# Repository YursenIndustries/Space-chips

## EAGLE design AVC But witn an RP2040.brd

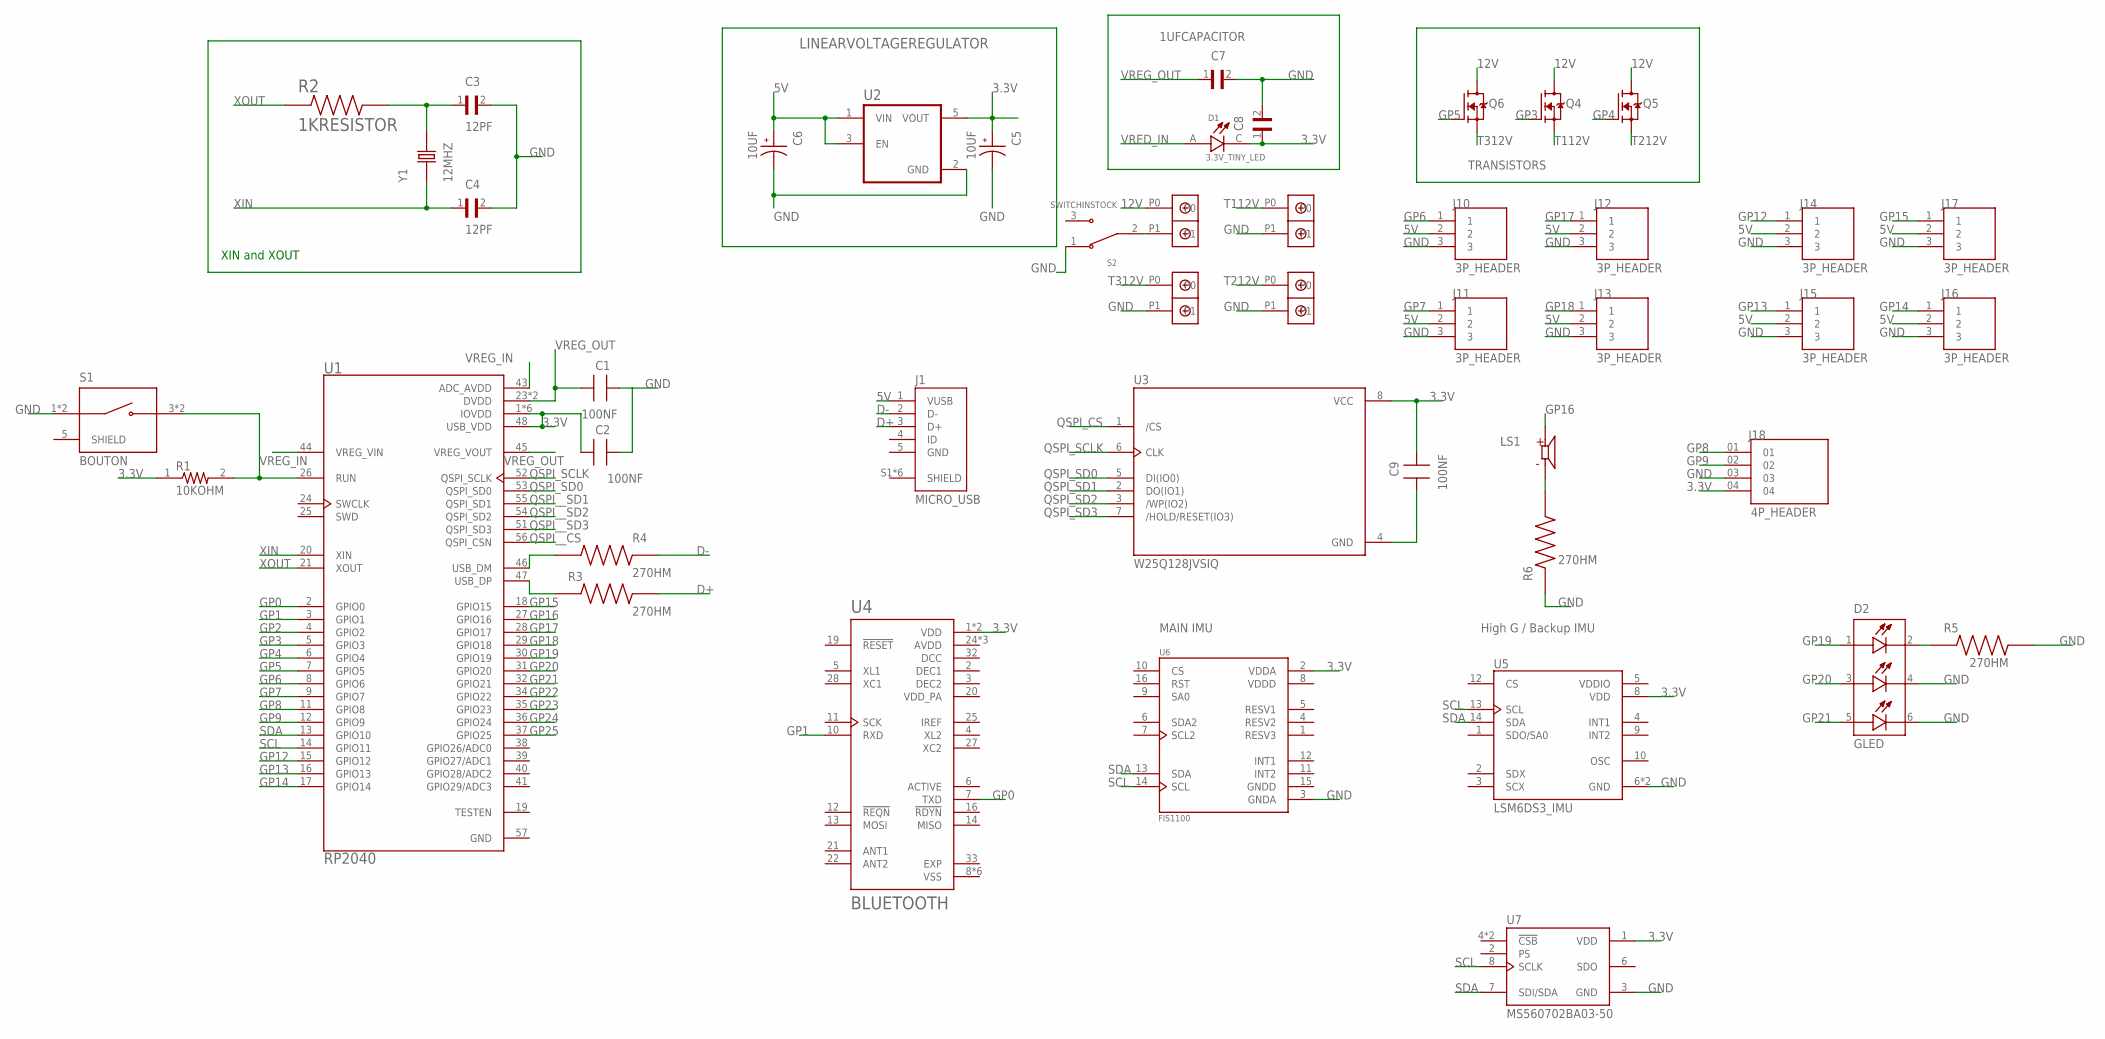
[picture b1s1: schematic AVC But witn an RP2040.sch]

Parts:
C1, C2, C9: 100NF; WCAP-CSST_885382207007
C3, C4: 12PF; CAPC1005X55N
C5, C6: 10UF; CAP_EEEFN1J100P
C7, C8: 1UFCAPACITOR
D1: 3.3V_TINY_LED; LED_IN-S124ARUW
D2: GLED
J1: MICRO_USB; FCI_10118193-0001LF
J10, J11, J12, J13, J14, J15, J16, J17: 3P_HEADER
J18: 4P_HEADER
LS1: 1.5V_BUZZER; SPKR_PKLCS1212E4001-R1
Q4, Q5, Q6: MOSFET20V; SOT95P240X111-3N
R1: 10KOHM; RESC1608X50N
R2: 1KRESISTOR
R3, R4, R5, R6: 270HM; RES_ERJU03F27R0V
S1: BOUTON; SW_1-1437565-9
S2: SWITCHINSTOCK; SW_EG1215AA
T_BATT: BLACK; BLACK`
T_PY1, T_PY2, T_PY3: BLACK; BLACK`
U1: RP2040; QFN40P700X700X90-57N
U2: LINEARVOLTAGEREGULATOR; SOT95P285X140-5N
U3: W25Q128JVSIQ; SOIC127P790X216-8N
U4: BLUETOOTH; QFN50P500X500X90-33N
U5: LSM6DS3_IMU; PQFN50P300X250X86-14N
U6: FIS1100; LGA16R50P4X4_330X330X100
U7: MS560702BA03-50; SON125P300X500X100-8N
Y1: 12MHZ; XTAL_ECS-120-S-5PX-TR

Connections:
3.3V: C2.1, C5.1, C8.1, C9.2, D1.C, J18.04, R1.1, U1.1 (IOVDD), U1.10 (IOVDD), U1.22 (IOVDD), U1.33 (IOVDD), U1.42 (IOVDD), U1.48 (USB_VDD), U1.49 (IOVDD), U2.5 (VOUT), U3.8 (VCC), U4.1 (VDD), U4.9 (VDD), U5.8 (VDD), U6.2 (VDDA), U7.1 (VDD)
5V: C6.1, J1.1 (VUSB), J10.2, J11.2, J12.2, J13.2, J14.2, J15.2, J16.2, J17.2, U2.1 (VIN), U2.3 (EN)
12V: Q4.3 (D), Q5.3 (D), Q6.3 (D), T_BATT.P0
AVDD: U4.24 (AVDD), U4.26 (AVDD), U4.29 (AVDD)
D+: J1.3 (D+), R3.2
D-: J1.2 (D-), R4.2
DCC: U4.32 (DCC)
DEC1: U4.2 (DEC1)
DEC2: U4.3 (DEC2)
EXP: U4.33 (EXP)
GND: C1.2, C2.2, C3.2, C4.2, C5.2, C6.2, C7.2, C8.2, D2.4 (GREEN_CATHODE), D2.6 (BLUE_CATHODE), J10.3, J11.3, J12.3, J13.3, J14.3, J15.3, J16.3, J17.3, J18.03, R5.2, R6.1, S1.1 (COM), S1.2 (COM), S2.1, T_PY1.P1, T_PY2.P1, T_PY3.P1, U1.57 (GND), U2.2 (GND), U5.6 (GND), U5.7 (GND), U6.3 (GNDA), U7.3 (GND)
GNDD: U6.15 (GNDD)
GP0: U1.2 (GPIO0), U4.7 (TXD)
GP1: U1.3 (GPIO1), U4.10 (RXD)
GP2: U1.4 (GPIO2)
GP3: Q4.1 (G), U1.5 (GPIO3)
GP4: Q5.1 (G), U1.6 (GPIO4)
GP5: Q6.1 (G), U1.7 (GPIO5)
GP6: J10.1, U1.8 (GPIO6)
GP7: J11.1, U1.9 (GPIO7)
GP8: J18.01, U1.11 (GPIO8)
GP9: J18.02, U1.12 (GPIO9)
GP12: J14.1, U1.15 (GPIO12)
GP13: J15.1, U1.16 (GPIO13)
GP14: J16.1, U1.17 (GPIO14)
GP15: J17.1, U1.18 (GPIO15)
GP16: LS1.P, U1.27 (GPIO16)
GP17: J12.1, U1.28 (GPIO17)
GP18: J13.1, U1.29 (GPIO18)
GP19: D2.1 (RED_ANODE), U1.30 (GPIO19)
GP20: D2.3 (GREEN_ANODE), U1.31 (GPIO20)
GP21: D2.5 (BLUE_ANODE), U1.32 (GPIO21)
GP22: U1.34 (GPIO22)
GP23: U1.35 (GPIO23)
GP24: U1.36 (GPIO24)
GP25: U1.37 (GPIO25)
unnamed: R1.2, S1.3 (NO), S1.4 (NO), U1.26 (RUN)
unnamed: C3.1, R2.2, Y1.2
unnamed: R3.1, U1.47 (USB_DP)
unnamed: C9.1, U3.4 (GND)
unnamed: R4.1, U1.46 (USB_DM)
unnamed: D2.2 (RED_CATHODE), R5.1
unnamed: LS1.N, R6.2
unnamed: S2.2, T_BATT.P1
QSPI_CS: U3.1 (/CS)
QSPI_SCLK: U1.52 (QSPI_SCLK), U3.6 (CLK)
QSPI_SD0: U1.53 (QSPI_SD0), U3.5 (DI(IO0))
QSPI_SD1: U3.2 (DO(IO1))
QSPI_SD2: U3.3 (/WP(IO2))
QSPI_SD3: U3.7 (/HOLD/RESET(IO3))
QSPI__CS: U1.56 (QSPI_CSN)
QSPI__SD1: U1.55 (QSPI_SD1)
QSPI__SD2: U1.54 (QSPI_SD2)
QSPI__SD3: U1.51 (QSPI_SD3)
RESV1: U6.5 (RESV1)
RESV2: U6.4 (RESV2)
RESV3: U6.1 (RESV3)
SCL: U1.14 (GPIO11), U5.13 (SCL), U6.14 (SCL), U7.8 (SCLK)
SDA: U1.13 (GPIO10), U5.14 (SDA), U6.13 (SDA), U7.7 (SDI/SDA)
T112V: Q4.2 (S), T_PY1.P0
T212V: Q5.2 (S), T_PY2.P0
T312V: Q6.2 (S), T_PY3.P0
VDDD: U6.8 (VDDD)
VDDIO: U5.5 (VDDIO)
VRED_IN: D1.A
VREG_IN: U1.43 (ADC_AVDD), U1.44 (VREG_VIN)
VREG_OUT: C1.1, C7.1, U1.23 (DVDD), U1.45 (VREG_VOUT), U1.50 (DVDD)
VSS: U4.8 (VSS), U4.17 (VSS), U4.18 (VSS), U4.23 (VSS), U4.30 (VSS), U4.31 (VSS)
XIN: C4.1, U1.20 (XIN), Y1.1
XOUT: R2.1, U1.21 (XOUT)

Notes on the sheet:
XIN and XOUT
MAIN IMU
High G / Backup IMU
TRANSISTORS

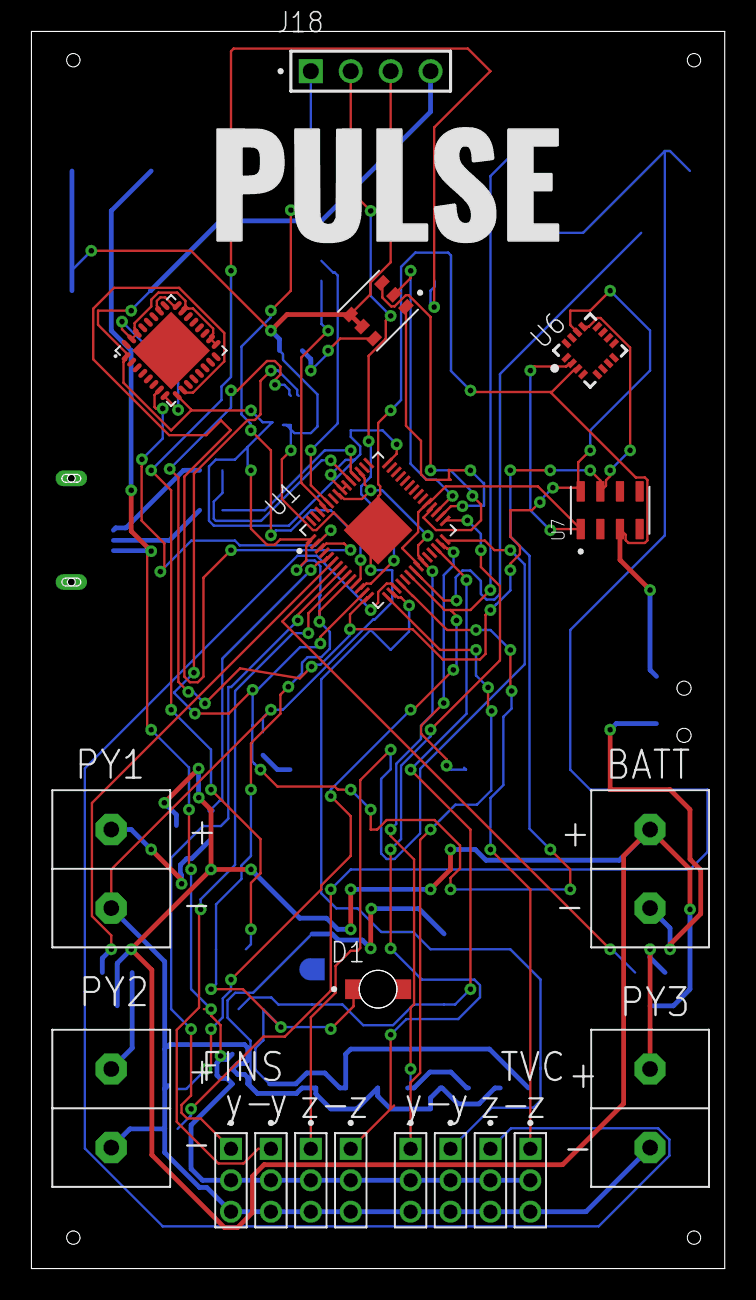
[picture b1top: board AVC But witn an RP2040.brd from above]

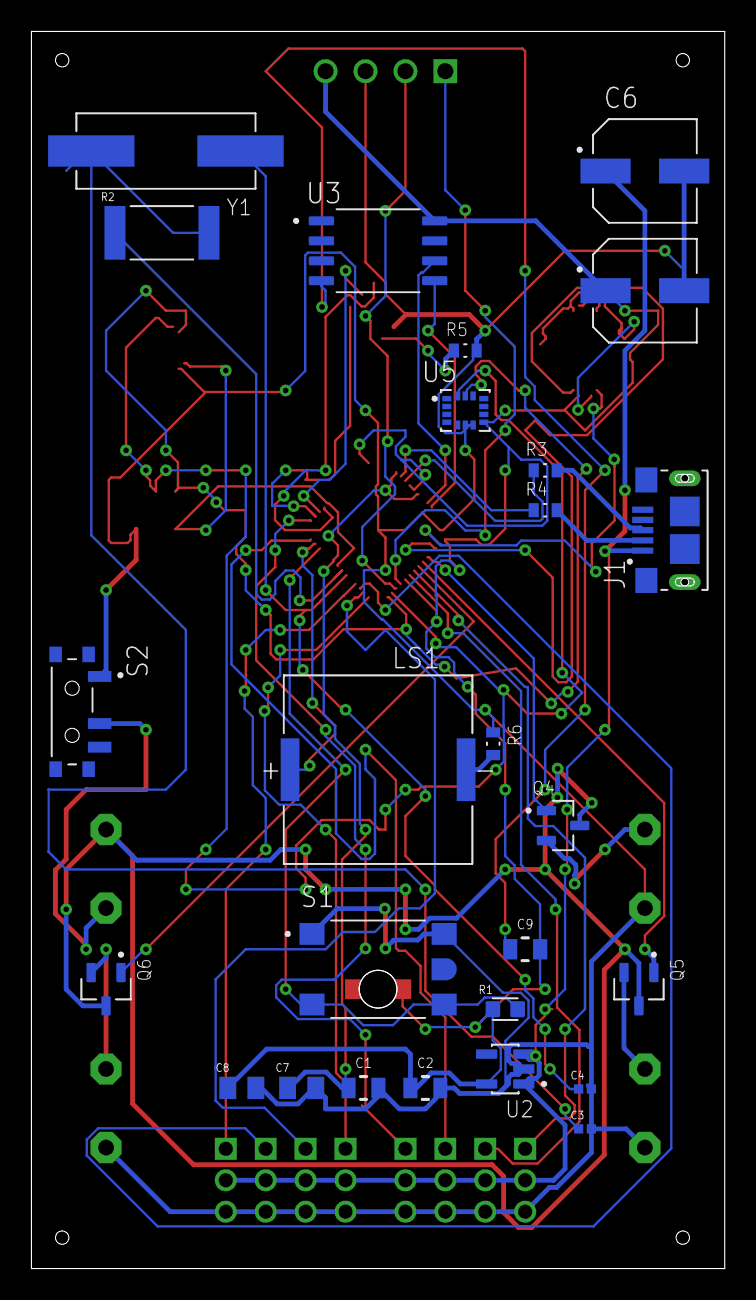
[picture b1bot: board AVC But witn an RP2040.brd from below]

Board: 2 copper layers, 44.1 x 78.7 mm, 45 parts (26 on the bottom side), 46 nets.
